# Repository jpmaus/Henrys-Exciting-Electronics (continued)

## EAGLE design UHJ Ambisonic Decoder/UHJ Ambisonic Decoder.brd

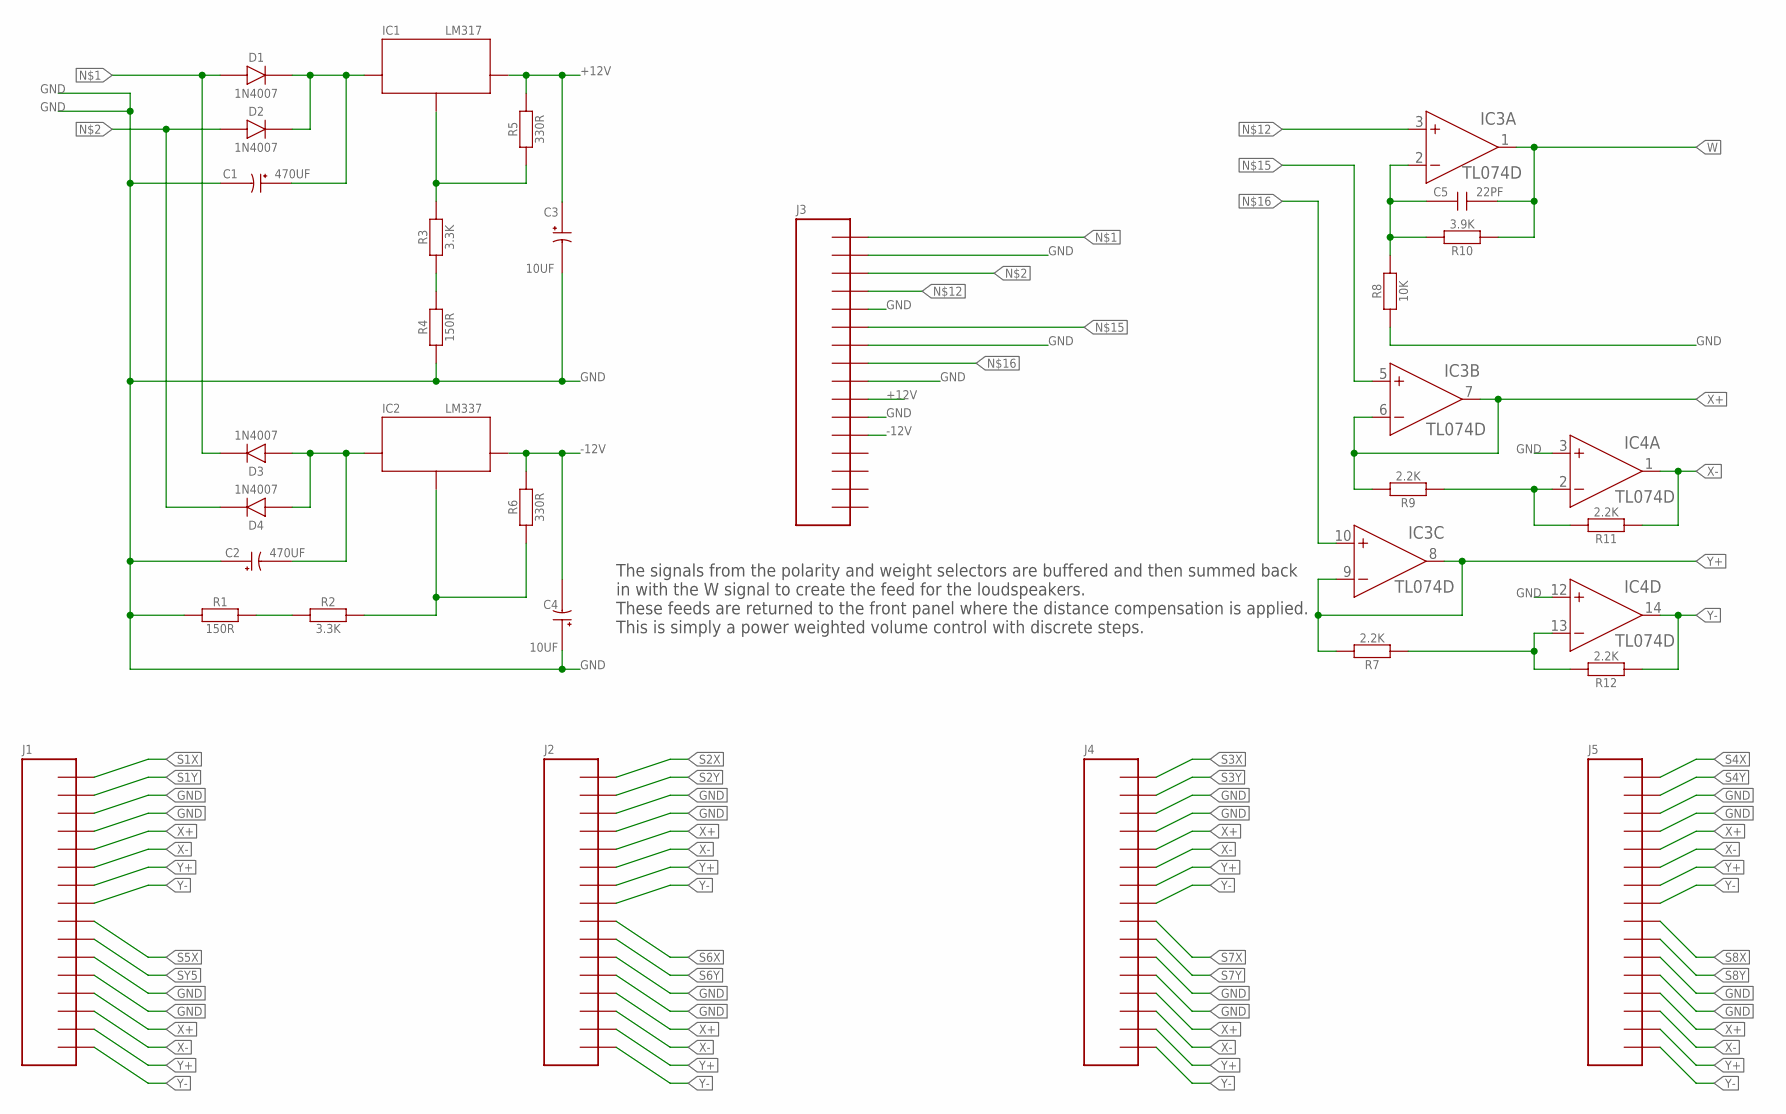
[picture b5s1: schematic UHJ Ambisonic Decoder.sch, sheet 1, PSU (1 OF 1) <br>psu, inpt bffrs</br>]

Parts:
C1, C2: 470UF; PANASONIC_E
C3, C4: 10UF; PANASONIC_E
C5: 22PF; CT6032
D1, D2, D3, D4: 1N4007; SOD123
IC1: LM317; SO08
IC2: LM337; SO08
IC3, IC4: TL074D; SO14
J1, J2, J3, J4, J5: CON_16; 2X08SMT
R1, R4: 150R; R6332W
R2, R3: 3.3K; R6332W
R5, R6: 330R; R6332W
R7, R9, R11, R12: 2.2K; R6332W
R8: 10K; R6332W
R10: 3.9K; R6332W

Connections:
+12V: C3.+ (1), IC1.1 (OUT), IC3.4 (V+), IC4.4 (V+), J3.10, R5.2; also elsewhere on the board
-12V: C4.- (2), IC2.1 (OUT), IC3.11 (V-), IC4.11 (V-), J3.12, R6.2; also elsewhere on the board
GND: C1.- (2), C2.+ (1), C3.- (2), C4.+ (1), IC4.3 (+IN), IC4.12 (+IN), J1.3, J1.4, J1.11, J1.12, J2.3, J2.4, J2.11, J2.12, J3.2, J3.5, J3.7, J3.9, J3.11, J4.3, J4.4, J4.11, J4.12, J5.3, J5.4, J5.11, J5.12, R1.1, R4.1, R8.1; also elsewhere on the board
unnamed: D1.A, D3.C, J3.1
unnamed: D2.A, D4.C, J3.3
unnamed: C1.+ (1), D1.C, D2.C, IC1.8 (IN)
unnamed: C2.- (2), D3.A, D4.A, IC2.8 (IN)
unnamed: IC1.2 (GND), IC1.3 (GND), IC1.6 (GND), IC1.7 (GND), R3.2, R5.1
unnamed: R3.1, R4.2
unnamed: IC2.2 (GND), IC2.3 (GND), IC2.6 (GND), IC2.7 (GND), R2.2, R6.1
unnamed: IC3.3 (+IN), J3.4
unnamed: C5.- (2), IC3.2 (-IN), R8.2, R10.2
unnamed: IC3.5 (+IN), J3.6
unnamed: IC3.10 (+IN), J3.8
unnamed: IC4.2 (-IN), R9.1, R11.2
unnamed: IC4.13 (-IN), R7.1, R12.2
unnamed: R1.2, R2.1
S1X: J1.1; also elsewhere on the board
S1Y: J1.2; also elsewhere on the board
S2X: J2.1; also elsewhere on the board
S2Y: J2.2; also elsewhere on the board
S3X: J4.1; also elsewhere on the board
S3Y: J4.2; also elsewhere on the board
S4X: J5.1; also elsewhere on the board
S4Y: J5.2; also elsewhere on the board
S5X: J1.9; also elsewhere on the board
S6X: J2.9; also elsewhere on the board
S6Y: J2.10; also elsewhere on the board
S7X: J4.9; also elsewhere on the board
S7Y: J4.10; also elsewhere on the board
S8X: J5.9; also elsewhere on the board
S8Y: J5.10; also elsewhere on the board
SY5: J1.10; also elsewhere on the board
W: C5.+ (1), IC3.1 (OUT), R10.1; also elsewhere on the board
X+: IC3.6 (-IN), IC3.7 (OUT), J1.5, J1.13, J2.5, J2.13, J4.5, J4.13, J5.5, J5.13, R9.2; also elsewhere on the board
X-: IC4.1 (OUT), J1.6, J1.14, J2.6, J2.14, J4.6, J4.14, J5.6, J5.14, R11.1; also elsewhere on the board
Y+: IC3.8 (OUT), IC3.9 (-IN), J1.7, J1.15, J2.7, J2.15, J4.7, J4.15, J5.7, J5.15, R7.2; also elsewhere on the board
Y-: IC4.14 (OUT), J1.8, J1.16, J2.8, J2.16, J4.8, J4.16, J5.8, J5.16, R12.1; also elsewhere on the board

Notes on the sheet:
The signals from the polarity and weight selectors are buffered and then summed back in with the W signal to create the feed for the loudspeakers. These feeds are returned to the front panel where the distance compensation is applied. This is simply a power weighted volume control with discrete ste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

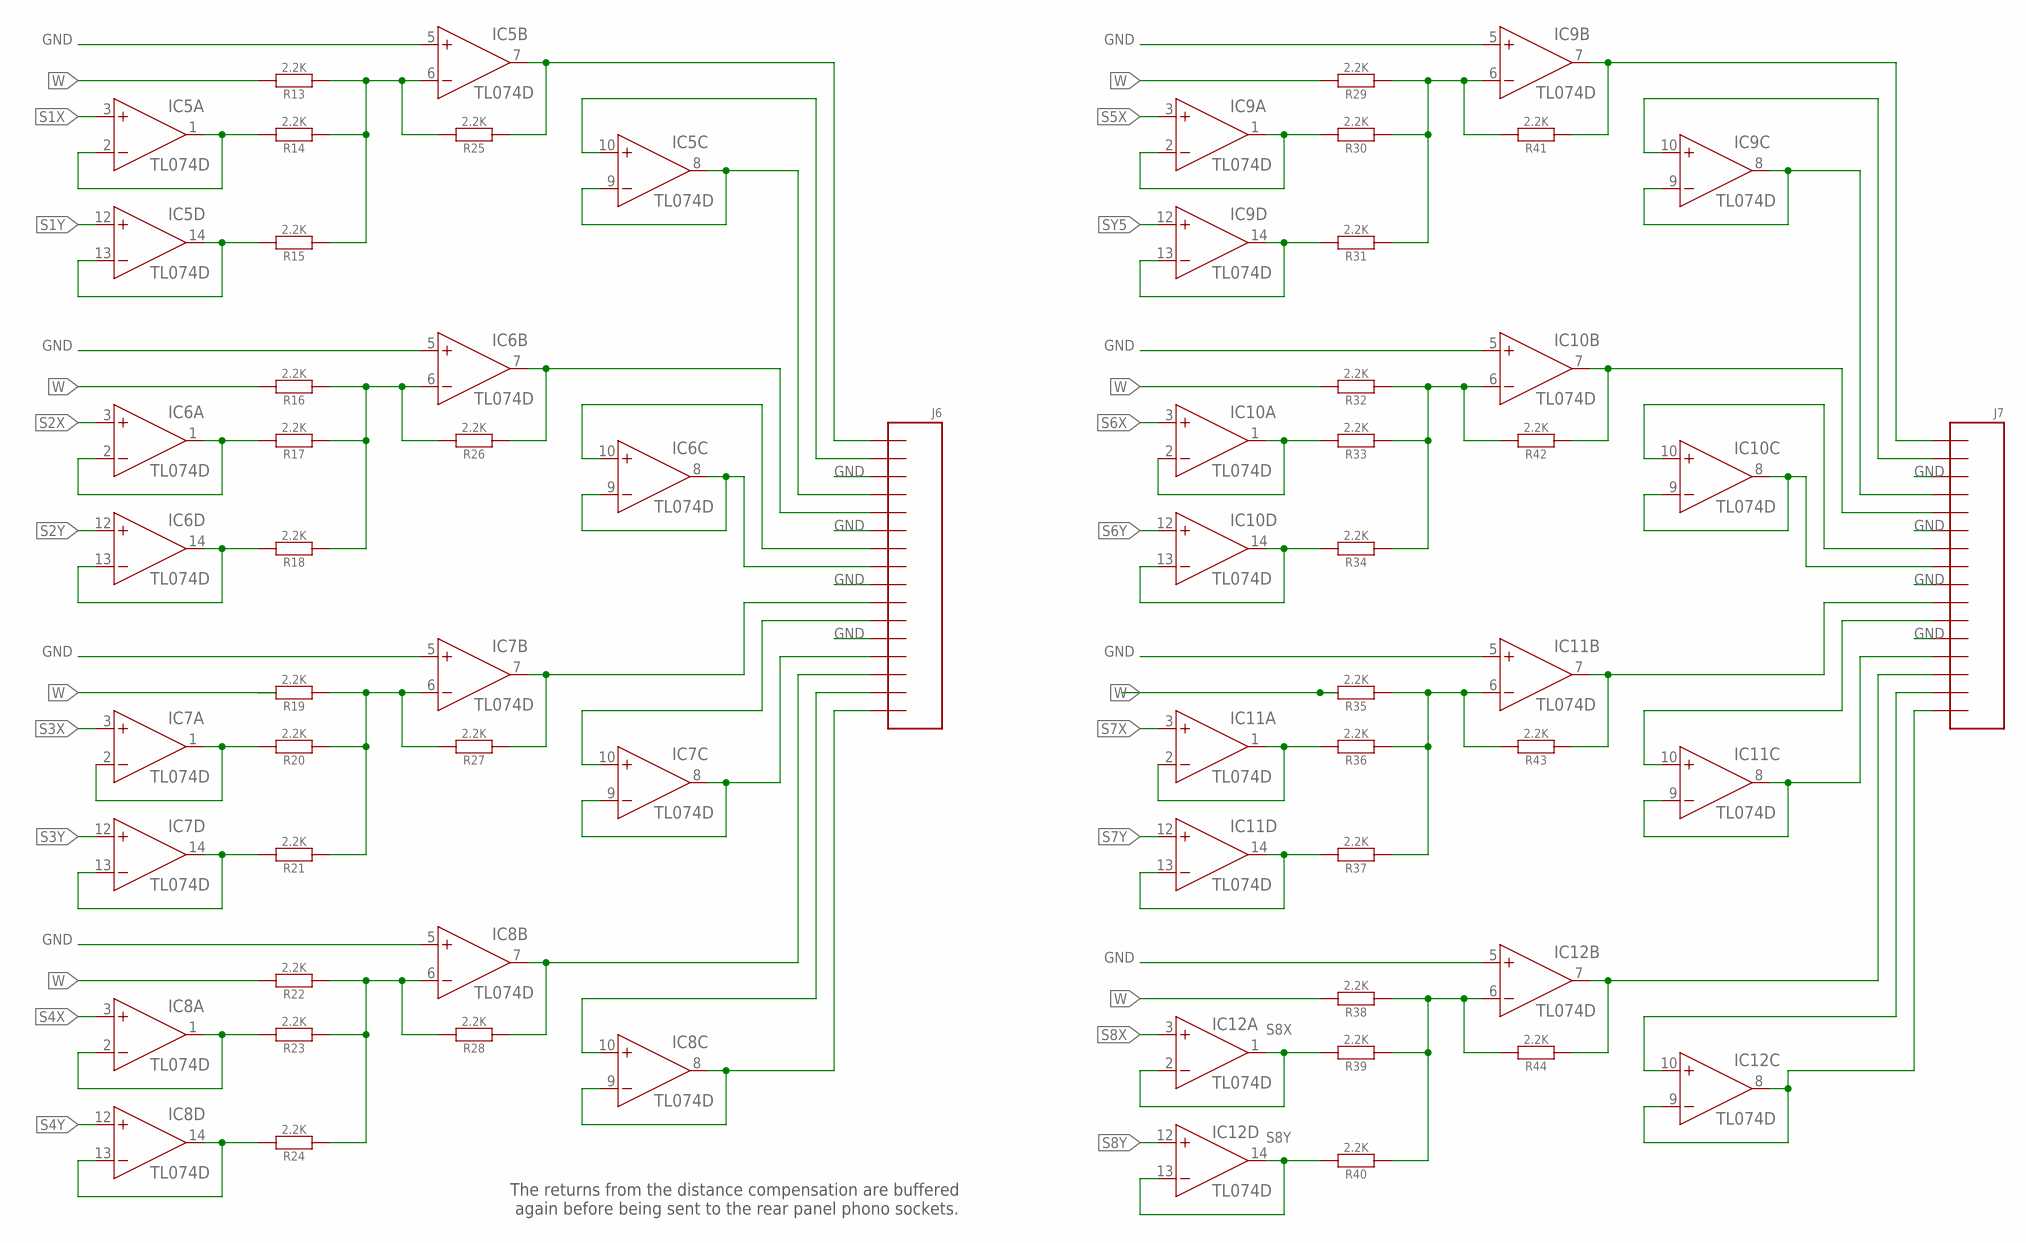
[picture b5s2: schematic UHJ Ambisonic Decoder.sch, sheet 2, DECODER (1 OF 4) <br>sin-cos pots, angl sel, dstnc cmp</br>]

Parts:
IC5, IC6, IC7, IC8, IC9, IC10, IC11, IC12: TL074D; SO14
J6, J7: CON_16; 2X08SMT
R13, R14, R15, R16, R17, R18, R19, R20, R21, R22, R23, R24, R25, R26, R27, R28, R29, R30, R31, R32, R33, R34, R35, R36, R37, R38, R39, R40, R41, R42, R43, R44: 2.2K; R6332W

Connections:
GND: IC5.5 (+IN), IC6.5 (+IN), IC7.5 (+IN), IC8.5 (+IN), IC9.5 (+IN), IC10.5 (+IN), IC11.5 (+IN), IC12.5 (+IN), J6.3, J6.6, J6.9, J6.12, J7.3, J7.6, J7.9, J7.12; also elsewhere on the board
unnamed: IC5.8 (OUT), IC5.9 (-IN), J6.4
unnamed: IC7.8 (OUT), IC7.9 (-IN), J6.13
unnamed: IC6.8 (OUT), IC6.9 (-IN), J6.8
unnamed: IC9.1 (OUT), IC9.2 (-IN), R30.2
unnamed: IC6.1 (OUT), IC6.2 (-IN), R17.2
unnamed: IC6.13 (-IN), IC6.14 (OUT), R18.2
unnamed: IC5.10 (+IN), J6.2
unnamed: IC6.10 (+IN), J6.7
unnamed: IC9.7 (OUT), J7.1, R41.1
unnamed: IC6.6 (-IN), R16.1, R17.1, R18.1, R26.2
unnamed: IC9.13 (-IN), IC9.14 (OUT), R31.2
unnamed: IC5.13 (-IN), IC5.14 (OUT), R15.2
unnamed: IC5.6 (-IN), R13.1, R14.1, R15.1, R25.2
unnamed: IC5.7 (OUT), J6.1, R25.1
unnamed: IC5.1 (OUT), IC5.2 (-IN), R14.2
unnamed: IC6.7 (OUT), J6.5, R26.1
unnamed: IC8.1 (OUT), IC8.2 (-IN), R23.2
unnamed: IC8.13 (-IN), IC8.14 (OUT), R24.2
unnamed: IC8.6 (-IN), R22.1, R23.1, R24.1, R28.2
unnamed: IC8.10 (+IN), J6.15
unnamed: IC7.13 (-IN), IC7.14 (OUT), R21.2
unnamed: IC7.6 (-IN), R19.1, R20.1, R21.1, R27.2
unnamed: IC7.7 (OUT), J6.10, R27.1
unnamed: IC7.1 (OUT), IC7.2 (-IN), R20.2
unnamed: IC8.7 (OUT), J6.14, R28.1
unnamed: IC10.10 (+IN), J7.7
unnamed: IC9.6 (-IN), R29.1, R30.1, R31.1, R41.2
unnamed: IC10.13 (-IN), IC10.14 (OUT), R34.2
unnamed: IC12.10 (+IN), J7.15
unnamed: IC10.6 (-IN), R32.1, R33.1, R34.1, R42.2
unnamed: IC12.8 (OUT), IC12.9 (-IN), J7.16
unnamed: IC10.7 (OUT), J7.5, R42.1
unnamed: IC10.1 (OUT), IC10.2 (-IN), R33.2
unnamed: IC12.1 (OUT), IC12.2 (-IN), R39.2
unnamed: IC12.13 (-IN), IC12.14 (OUT), R40.2
unnamed: IC12.6 (-IN), R38.1, R39.1, R40.1, R44.2
unnamed: IC11.8 (OUT), IC11.9 (-IN), J7.13
unnamed: IC11.13 (-IN), IC11.14 (OUT), R37.2
unnamed: IC11.6 (-IN), R35.1, R36.1, R37.1, R43.2
unnamed: IC11.7 (OUT), J7.10, R43.1
unnamed: IC11.1 (OUT), IC11.2 (-IN), R36.2
unnamed: IC8.8 (OUT), IC8.9 (-IN), J6.16
unnamed: IC9.8 (OUT), IC9.9 (-IN), J7.4
unnamed: IC7.10 (+IN), J6.11
unnamed: IC12.7 (OUT), J7.14, R44.1
unnamed: IC10.8 (OUT), IC10.9 (-IN), J7.8
unnamed: IC9.10 (+IN), J7.2
unnamed: IC11.10 (+IN), J7.11
S1X: IC5.3 (+IN); also elsewhere on the board
S1Y: IC5.12 (+IN); also elsewhere on the board
S2X: IC6.3 (+IN); also elsewhere on the board
S2Y: IC6.12 (+IN); also elsewhere on the board
S3X: IC7.3 (+IN); also elsewhere on the board
S3Y: IC7.12 (+IN); also elsewhere on the board
S4X: IC8.3 (+IN); also elsewhere on the board
S4Y: IC8.12 (+IN); also elsewhere on the board
S5X: IC9.3 (+IN); also elsewhere on the board
S6X: IC10.3 (+IN); also elsewhere on the board
S6Y: IC10.12 (+IN); also elsewhere on the board
S7X: IC11.3 (+IN); also elsewhere on the board
S7Y: IC11.12 (+IN); also elsewhere on the board
S8X: IC12.3 (+IN); also elsewhere on the board
S8Y: IC12.12 (+IN); also elsewhere on the board
SY5: IC9.12 (+IN); also elsewhere on the board
W: R13.2, R16.2, R19.2, R22.2, R29.2, R32.2, R35.2, R38.2; also elsewhere on the board

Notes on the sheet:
The returns from the distance compensation are buffered again before being sent to the rear panel phono sockets.

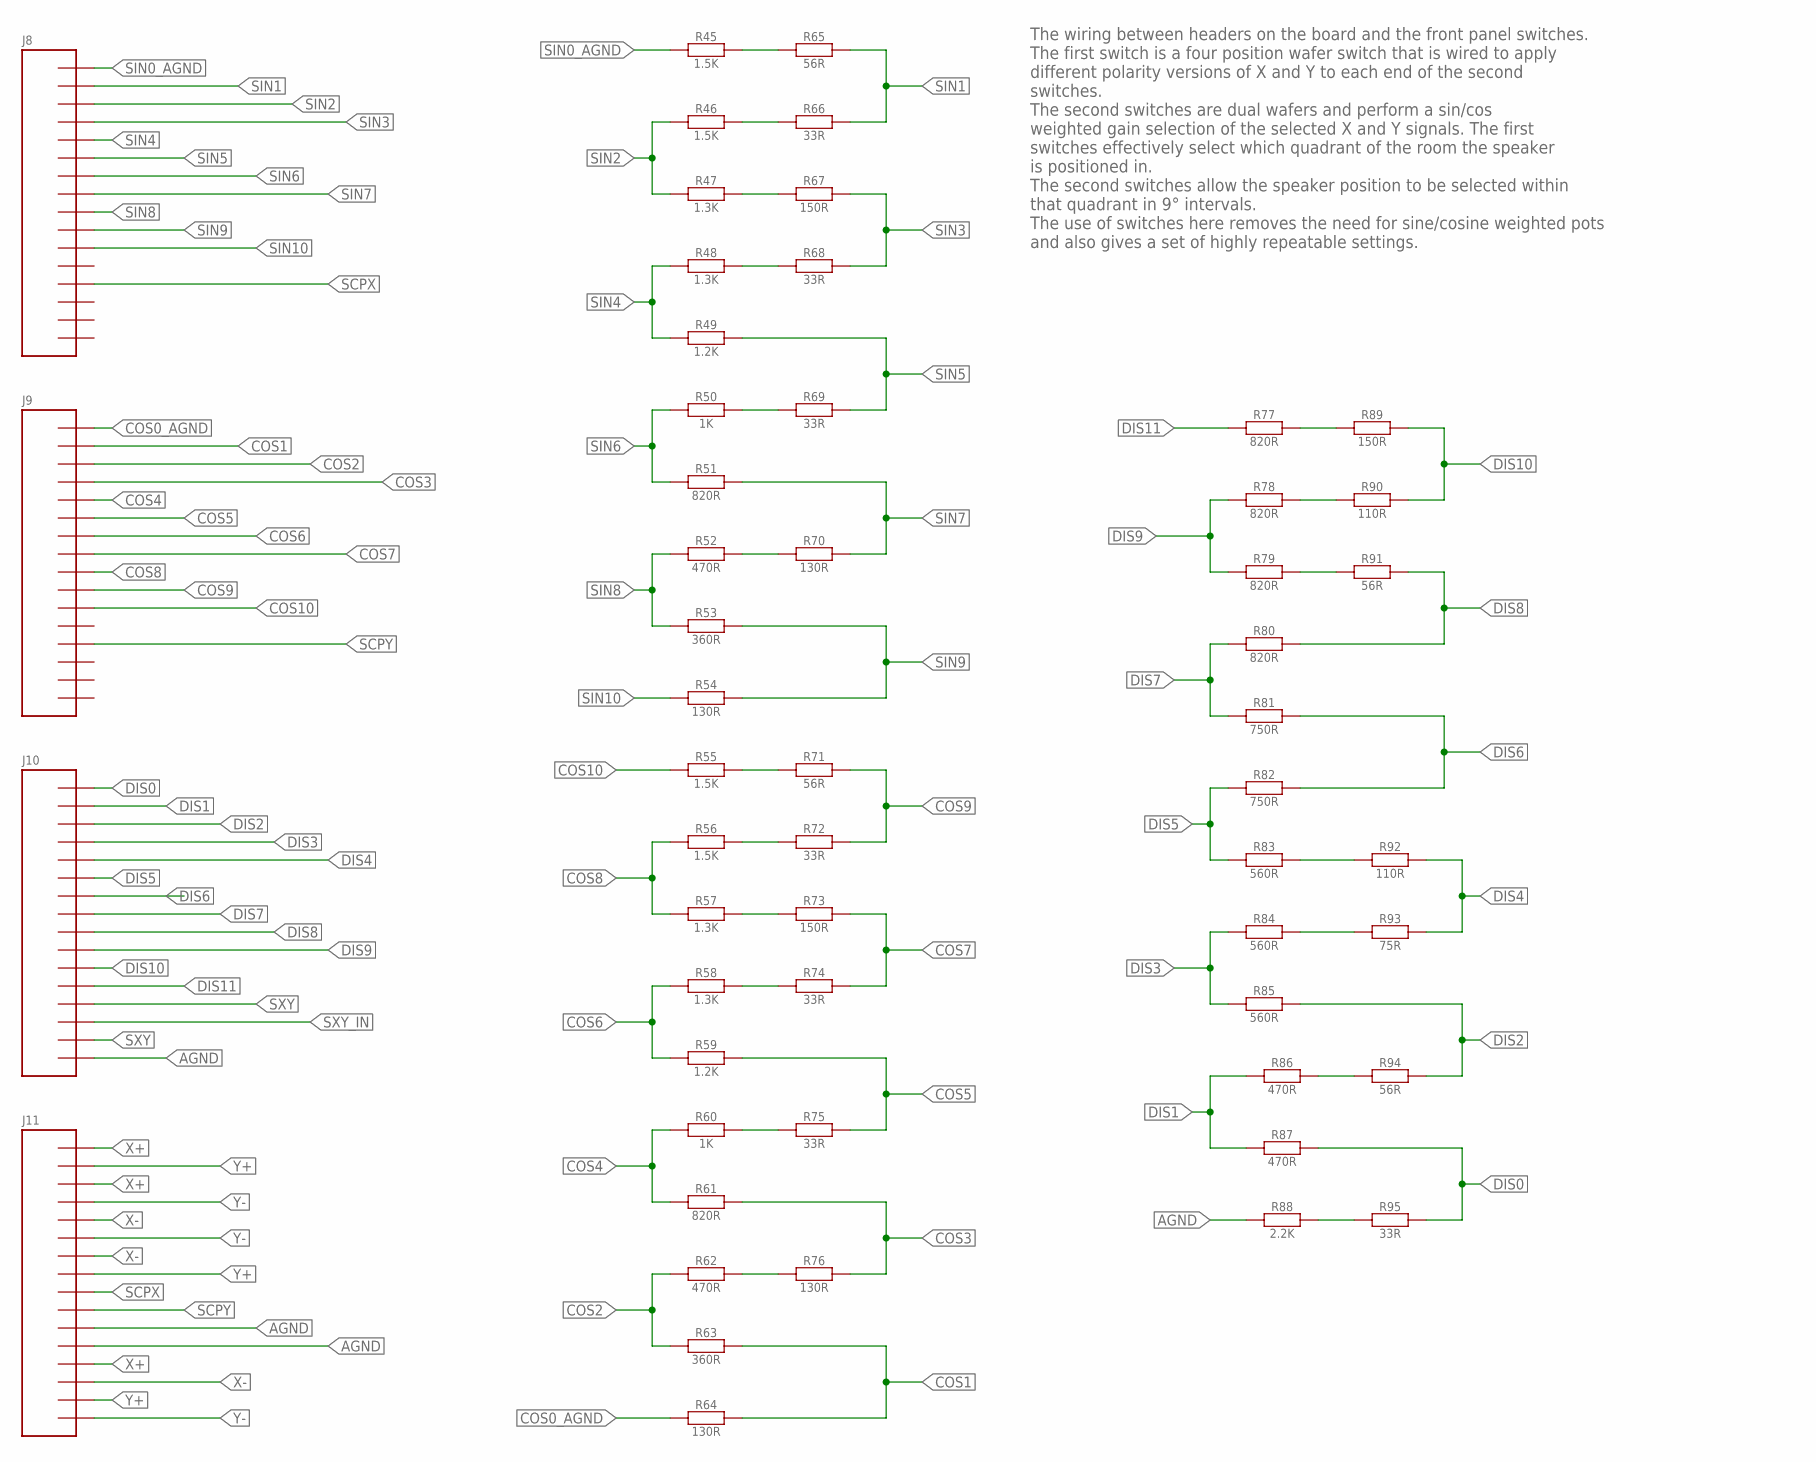
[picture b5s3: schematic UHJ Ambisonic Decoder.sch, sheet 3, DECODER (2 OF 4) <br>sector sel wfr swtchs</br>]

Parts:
J8, J9, J10, J11: CON_16; 2X08SMT
R45, R46, R55, R56: 1.5K; R6332W
R47, R48, R57, R58: 1.3K; R6332W
R49, R59: 1.2K; R6332W
R50, R60: 1K; R6332W
R51, R61, R77, R78, R79, R80: 820R; R6332W
R52, R62, R86, R87: 470R; R6332W
R53, R63: 360R; R6332W
R54, R64, R70, R76: 130R; R6332W
R65, R71, R91, R94: 56R; R6332W
R66, R68, R69, R72, R74, R75, R95: 33R; R6332W
R67, R73, R89: 150R; R6332W
R81, R82: 750R; R6332W
R83, R84, R85: 560R; R6332W
R88: 2.2K; R6332W
R90, R92: 110R; R6332W
R93: 75R; R6332W

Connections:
AGND: J10.16, J11.11, J11.12, R88.1
COS0_AGND: J9.1, R64.1
COS1: J9.2, R63.2, R64.2
COS2: J9.3, R62.1, R63.1
COS3: J9.4, R61.2, R76.2
COS4: J9.5, R60.1, R61.1
COS5: J9.6, R59.2, R75.2
COS6: J9.7, R58.1, R59.1
COS7: J9.8, R73.2, R74.2
COS8: J9.9, R56.1, R57.1
COS9: J9.10, R71.2, R72.2
COS10: J9.11, R55.1
DIS0: J10.1, R87.2, R95.2
DIS1: J10.2, R86.1, R87.1
DIS2: J10.3, R85.2, R94.2
DIS3: J10.4, R84.1, R85.1
DIS4: J10.5, R92.2, R93.2
DIS5: J10.6, R82.1, R83.1
DIS6: J10.7, R81.2, R82.2
DIS7: J10.8, R80.1, R81.1
DIS8: J10.9, R80.2, R91.2
DIS9: J10.10, R78.1, R79.1
DIS10: J10.11, R89.2, R90.2
DIS11: J10.12, R77.1
unnamed: R45.2, R65.1
unnamed: R46.2, R66.1
unnamed: R47.2, R67.1
unnamed: R48.2, R68.1
unnamed: R50.2, R69.1
unnamed: R52.2, R70.1
unnamed: R55.2, R71.1
unnamed: R56.2, R72.1
unnamed: R57.2, R73.1
unnamed: R58.2, R74.1
unnamed: R60.2, R75.1
unnamed: R62.2, R76.1
unnamed: R77.2, R89.1
unnamed: R78.2, R90.1
unnamed: R79.2, R91.1
unnamed: R83.2, R92.1
unnamed: R84.2, R93.1
unnamed: R86.2, R94.1
unnamed: R88.2, R95.1
SCPX: J8.13, J11.9
SCPY: J9.13, J11.10
SIN0_AGND: J8.1, R45.1
SIN1: J8.2, R65.2, R66.2
SIN2: J8.3, R46.1, R47.1
SIN3: J8.4, R67.2, R68.2
SIN4: J8.5, R48.1, R49.1
SIN5: J8.6, R49.2, R69.2
SIN6: J8.7, R50.1, R51.1
SIN7: J8.8, R51.2, R70.2
SIN8: J8.9, R52.1, R53.1
SIN9: J8.10, R53.2, R54.2
SIN10: J8.11, R54.1
SXY: J10.13, J10.15
SXY_IN: J10.14
X+: J11.1, J11.3, J11.13; also elsewhere on the board
X-: J11.5, J11.7, J11.14; also elsewhere on the board
Y+: J11.2, J11.8, J11.15; also elsewhere on the board
Y-: J11.4, J11.6, J11.16; also elsewhere on the board

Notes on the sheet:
The wiring between headers on the board and the front panel switches. The first switch is a four position wafer switch that is wired to apply different polarity versions of X and Y to each end of the second switches. The second switches are dual wafers and perform a sin/cos weighted gain selection 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

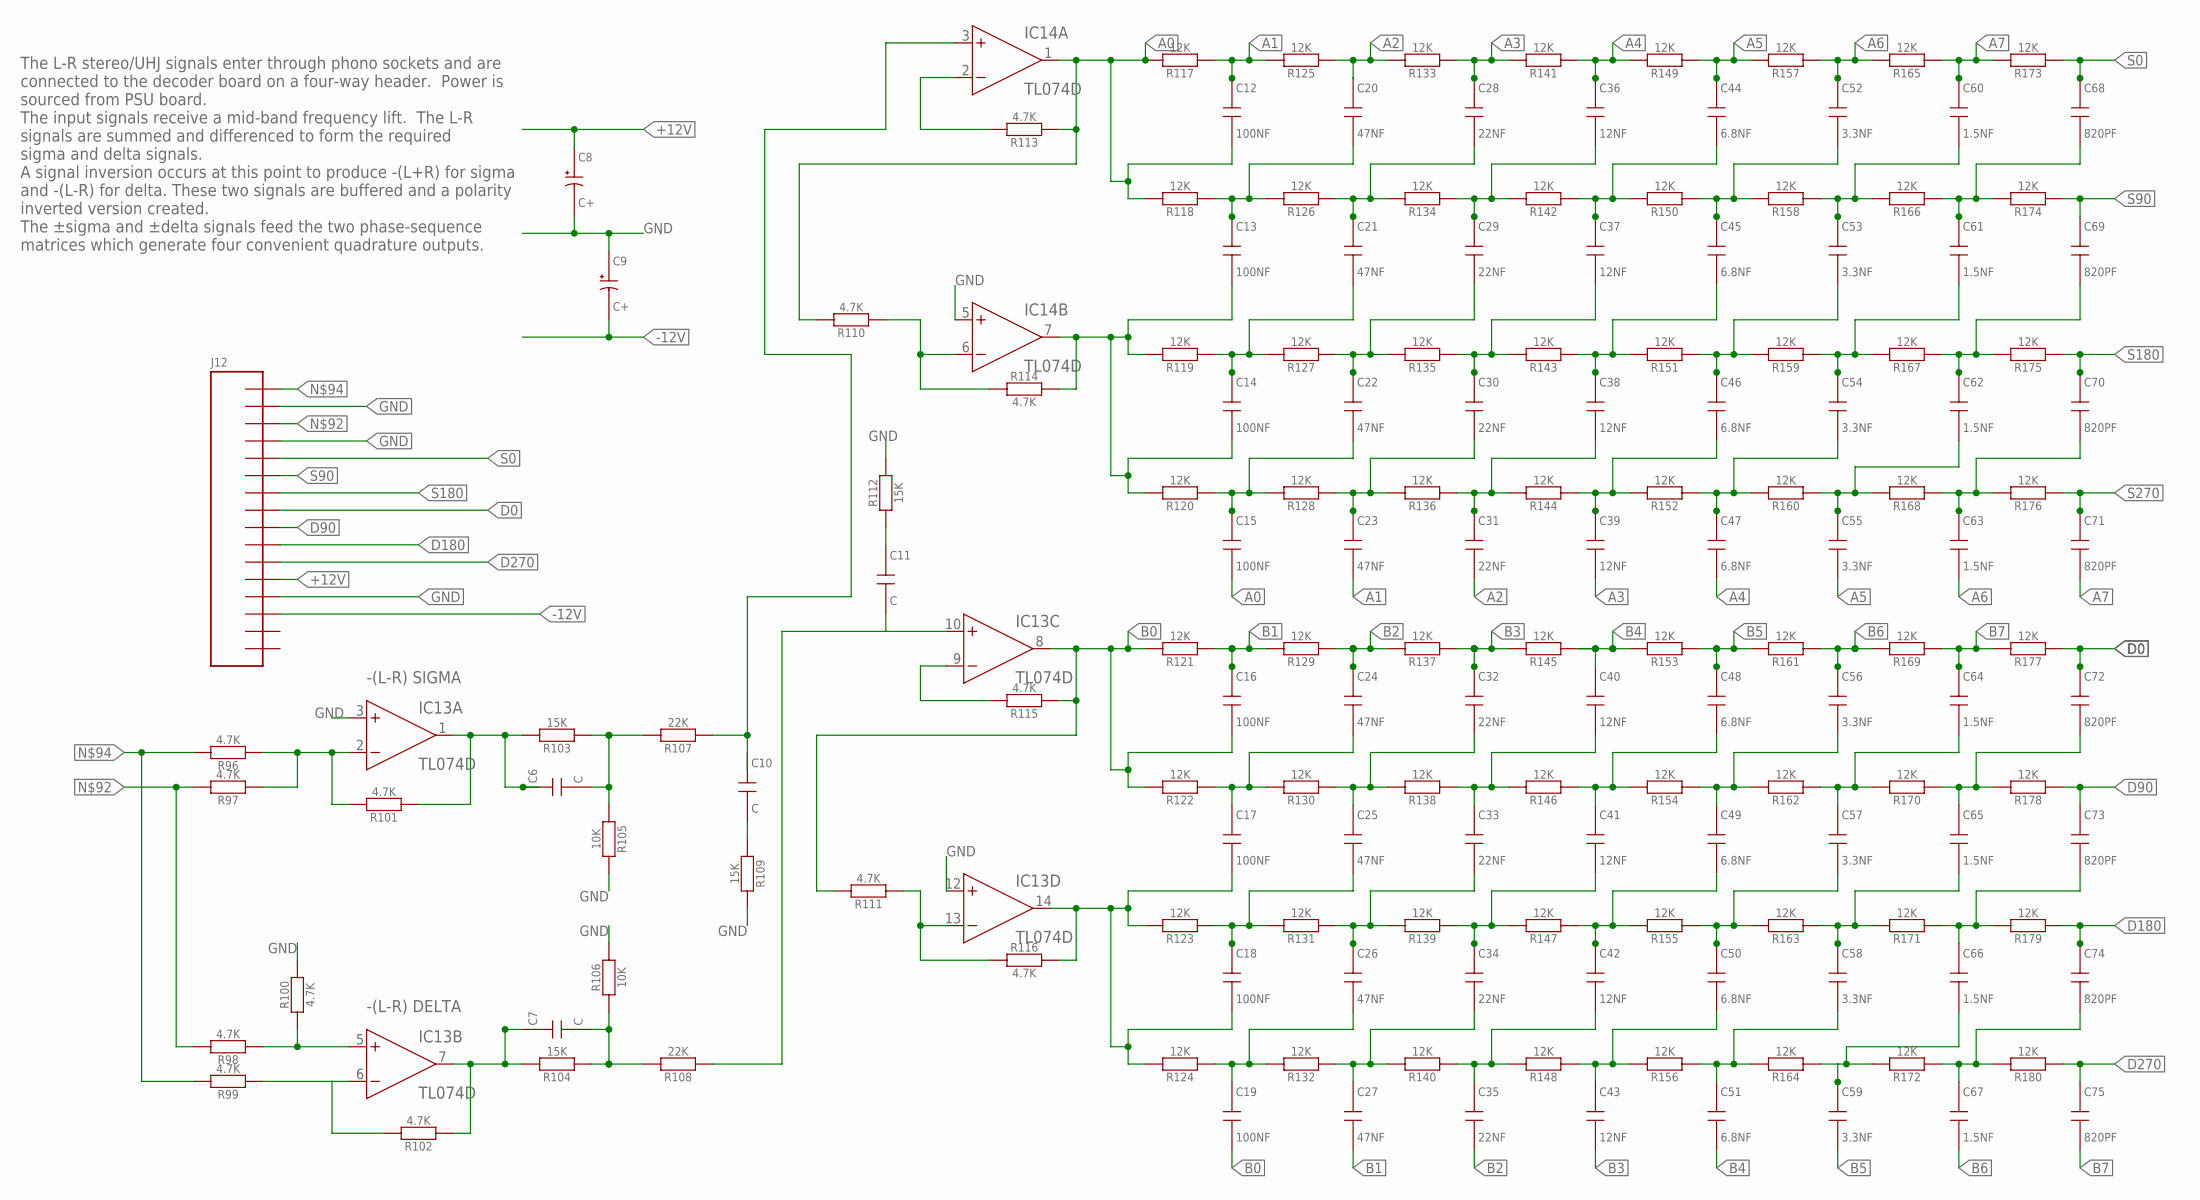
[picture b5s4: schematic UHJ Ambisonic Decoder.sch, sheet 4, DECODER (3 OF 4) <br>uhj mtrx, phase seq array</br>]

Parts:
C6, C7, C10, C11: C; CT6032
C8, C9: C+; PANASONIC_E
C12, C13, C14, C15, C16, C17, C18, C19: 100NF; CT6032
C20, C21, C22, C23, C24, C25, C26, C27: 47NF; CT6032
C28, C29, C30, C31, C32, C33, C34, C35: 22NF; CT6032
C36, C37, C38, C39, C40, C41, C42, C43: 12NF; CT6032
C44, C45, C46, C47, C48, C49, C50, C51: 6.8NF; CT6032
C52, C53, C54, C55, C56, C57, C58, C59: 3.3NF; CT6032
C60, C61, C62, C63, C64, C65, C66, C67: 1.5NF; CT6032
C68, C69, C70, C71, C72, C73, C74, C75: 820PF; CT6032
IC13, IC14: TL074D; SO14
J12: CON_16; 2X08SMT
R96, R97, R98, R99, R100, R101, R102, R110, R111, R113, R114, R115, R116: 4.7K; R6332W
R103, R104, R109, R112: 15K; R6332W
R105, R106: 10K; R6332W
R107, R108: 22K; R6332W
R117, R118, R119, R120, R121, R122, R123, R124, R125, R126, R127, R128, R129, R130, R131, R132, R133, R134, R135, R136, R137, R138, R139, R140, R141, R142, R143, R144, R145, R146, R147, R148, R149, R150, R151, R152, R153, R154, R155, R156, R157, R158, R159, R160, R161, R162, R163, R164, R165, R166, R167, R168, R169, R170, R171, R172, R173, R174, R175, R176, R177, R178, R179, R180: 12K; R6332W

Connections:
+12V: C8.+ (1), IC13.4 (V+), IC14.4 (V+), J12.12; also elsewhere on the board
-12V: C9.- (2), IC13.11 (V-), IC14.11 (V-), J12.14; also elsewhere on the board
A0: C12.- (2), C15.- (2), IC14.1 (OUT), R110.2, R113.1, R117.2, R118.2
A1: C12.+ (1), C23.- (2), R117.1, R125.2
A2: C20.+ (1), C31.- (2), R125.1, R133.2
A3: C28.+ (1), C39.- (2), R133.1, R141.2
A4: C36.+ (1), C47.- (2), R141.1, R149.2
A5: C44.+ (1), C55.- (2), R149.1, R157.2
A6: C52.+ (1), C63.- (2), R157.1, R165.2
A7: C60.+ (1), C71.- (2), R165.1, R173.2
B0: C16.- (2), C19.- (2), IC13.8 (OUT), R111.2, R115.1, R121.2, R122.2
B1: C16.+ (1), C27.- (2), R121.1, R129.2
B2: C24.+ (1), C35.- (2), R129.1, R137.2
B3: C32.+ (1), C43.- (2), R137.1, R145.2
B4: C40.+ (1), C51.- (2), R145.1, R153.2
B5: C48.+ (1), C59.- (2), R153.1, R161.2
B6: C56.+ (1), C67.- (2), R161.1, R169.2
B7: C64.+ (1), C75.- (2), R169.1, R177.2
D0: C72.+ (1), J12.8, R177.1; also elsewhere on the board
D90: C73.+ (1), J12.9, R178.1; also elsewhere on the board
D180: C74.+ (1), J12.10, R179.1
D270: C75.+ (1), J12.11, R180.1
GND: C8.- (2), C9.+ (1), IC13.3 (+IN), IC14.5 (+IN), J12.2, J12.4, J12.13, R100.2, R105.2, R106.2, R109.2, R112.2; also elsewhere on the board
unnamed: C59.+ (1), C66.- (2), R164.1, R172.2
unnamed: C65.+ (1), C72.- (2), R170.1, R178.2
unnamed: C55.+ (1), C62.- (2), R160.1, R168.2
unnamed: C13.+ (1), C20.- (2), R118.1, R126.2
unnamed: C21.+ (1), C28.- (2), R126.1, R134.2
unnamed: C29.+ (1), C36.- (2), R134.1, R142.2
unnamed: C37.+ (1), C44.- (2), R142.1, R150.2
unnamed: C45.+ (1), C52.- (2), R150.1, R158.2
unnamed: C53.+ (1), C60.- (2), R158.1, R166.2
unnamed: C61.+ (1), C68.- (2), R166.1, R174.2
unnamed: C14.+ (1), C21.- (2), R119.1, R127.2
unnamed: C22.+ (1), C29.- (2), R127.1, R135.2
unnamed: C30.+ (1), C37.- (2), R135.1, R143.2
unnamed: C38.+ (1), C45.- (2), R143.1, R151.2
unnamed: C46.+ (1), C53.- (2), R151.1, R159.2
unnamed: C54.+ (1), C61.- (2), R159.1, R167.2
unnamed: C62.+ (1), C69.- (2), R167.1, R175.2
unnamed: C15.+ (1), C22.- (2), R120.1, R128.2
unnamed: C23.+ (1), C30.- (2), R128.1, R136.2
unnamed: C31.+ (1), C38.- (2), R136.1, R144.2
unnamed: C39.+ (1), C46.- (2), R144.1, R152.2
unnamed: C47.+ (1), C54.- (2), R152.1, R160.2
unnamed: C63.+ (1), C70.- (2), R168.1, R176.2
unnamed: C17.+ (1), C24.- (2), R122.1, R130.2
unnamed: C25.+ (1), C32.- (2), R130.1, R138.2
unnamed: C33.+ (1), C40.- (2), R138.1, R146.2
unnamed: C41.+ (1), C48.- (2), R146.1, R154.2
unnamed: C49.+ (1), C56.- (2), R154.1, R162.2
unnamed: C57.+ (1), C64.- (2), R162.1, R170.2
unnamed: C18.+ (1), C25.- (2), R123.1, R131.2
unnamed: C26.+ (1), C33.- (2), R131.1, R139.2
unnamed: C34.+ (1), C41.- (2), R139.1, R147.2
unnamed: C42.+ (1), C49.- (2), R147.1, R155.2
unnamed: C50.+ (1), C57.- (2), R155.1, R163.2
unnamed: C58.+ (1), C65.- (2), R163.1, R171.2
unnamed: C66.+ (1), C73.- (2), R171.1, R179.2
unnamed: C19.+ (1), C26.- (2), R124.1, R132.2
unnamed: C27.+ (1), C34.- (2), R132.1, R140.2
unnamed: C35.+ (1), C42.- (2), R140.1, R148.2
unnamed: C43.+ (1), C50.- (2), R148.1, R156.2
unnamed: C51.+ (1), C58.- (2), R156.1, R164.2
unnamed: IC13.2 (-IN), R96.1, R97.1, R101.2
unnamed: IC13.6 (-IN), R99.1, R102.2
unnamed: J12.3, R97.2, R98.2
unnamed: IC13.5 (+IN), R98.1, R100.1
unnamed: J12.1, R96.2, R99.2
unnamed: C67.+ (1), C74.- (2), R172.1, R180.2
unnamed: IC13.9 (-IN), R115.2
unnamed: C17.- (2), C18.- (2), IC13.14 (OUT), R116.2, R123.2, R124.2
unnamed: IC13.13 (-IN), R111.1, R116.1
unnamed: C6.- (2), R103.1, R105.1, R107.2
unnamed: C10.+ (1), IC14.3 (+IN), R107.1
unnamed: C10.- (2), R109.1
unnamed: C7.- (2), R104.1, R106.1, R108.2
unnamed: C11.- (2), IC13.10 (+IN), R108.1
unnamed: C11.+ (1), R112.1
unnamed: IC14.2 (-IN), R113.2
unnamed: C13.- (2), C14.- (2), IC14.7 (OUT), R114.2, R119.2, R120.2
unnamed: IC14.6 (-IN), R110.1, R114.1
S0: C68.+ (1), J12.5, R173.1; also elsewhere on the board
S90: C69.+ (1), J12.6, R174.1; also elsewhere on the board
S180: C70.+ (1), J12.7, R175.1
S270: C71.+ (1), R176.1
X-: C6.+ (1), IC13.1 (OUT), R101.1, R103.2; also elsewhere on the board
Y-: C7.+ (1), IC13.7 (OUT), R102.1, R104.2; also elsewhere on the board

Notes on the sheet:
The L-R stereo/UHJ signals enter through phono sockets and are connected to the decoder board on a four-way header. Power is sourced from PSU board. The input signals receive a mid-band frequency lift. The L-R signals are summed and differenced to form the required sigma and delta signals. A signal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
-(L-R) SIGMA
-(L-R) DELTA

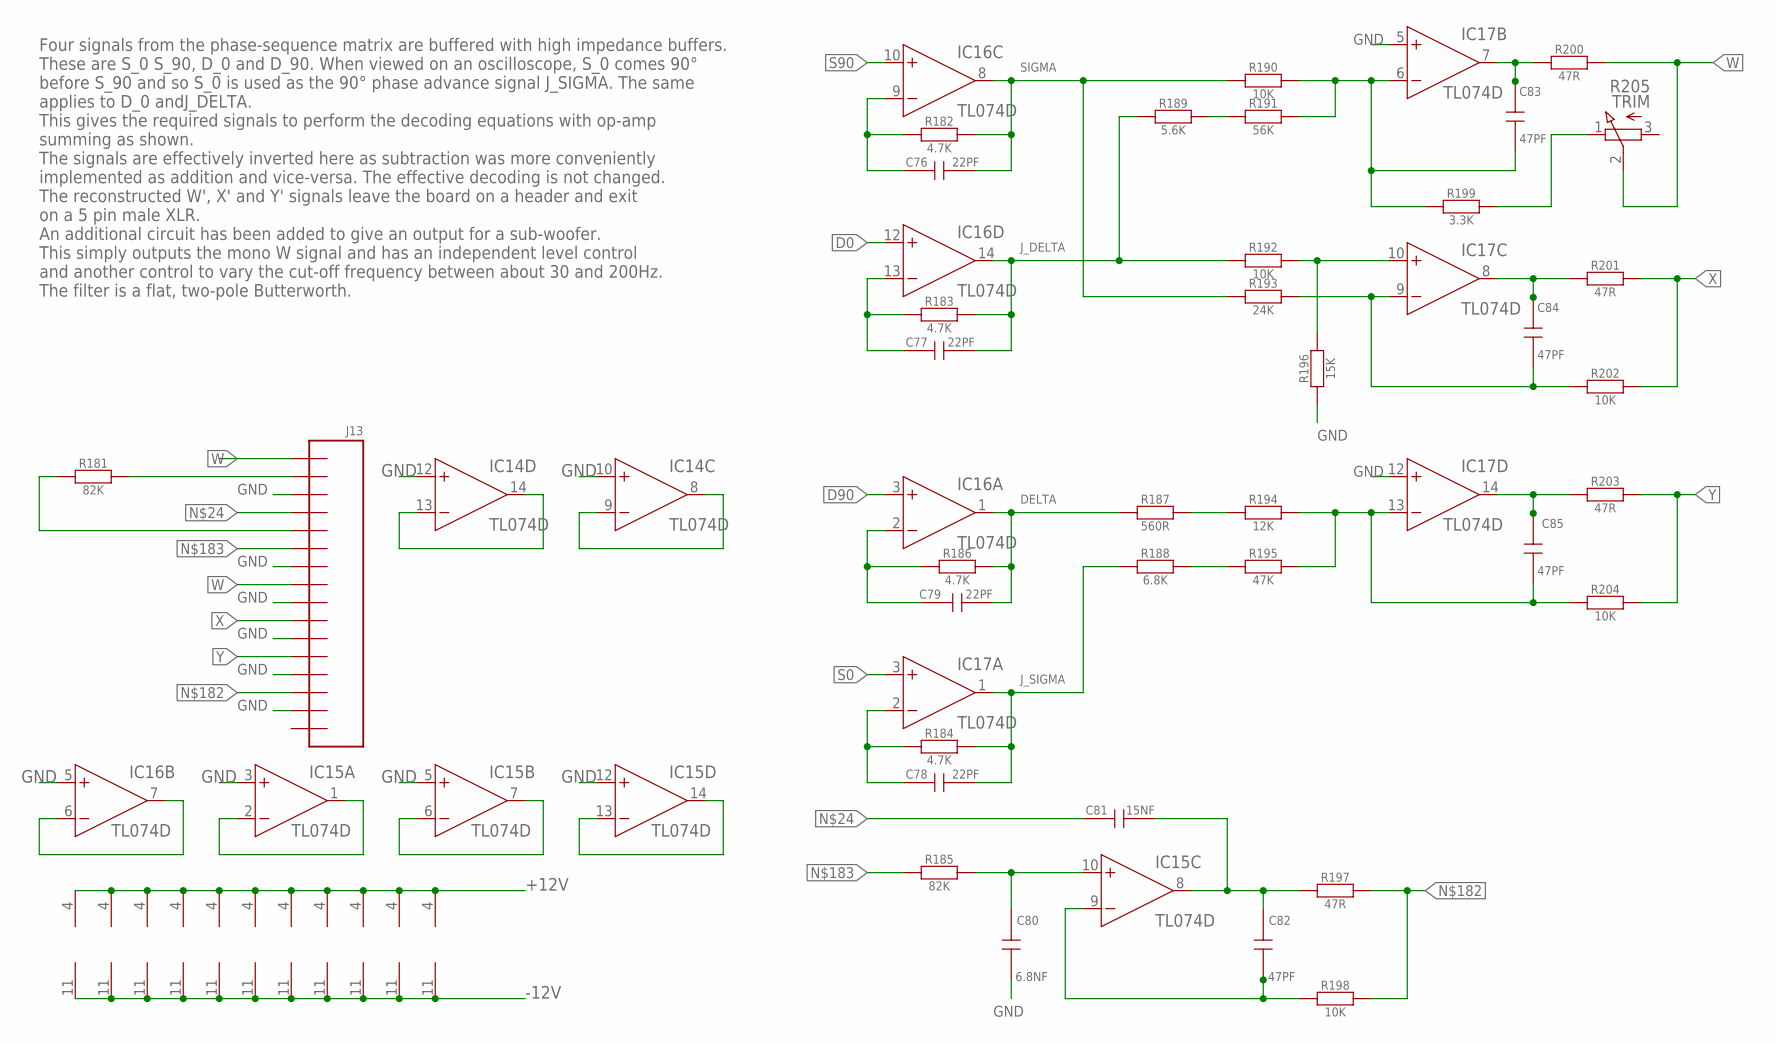
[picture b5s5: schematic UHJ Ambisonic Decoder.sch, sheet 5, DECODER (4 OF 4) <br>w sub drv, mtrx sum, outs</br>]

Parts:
C76, C77, C78, C79: 22PF; CT6032
C80: 6.8NF; CT6032
C81: 15NF; CT6032
C82, C83, C84, C85: 47PF; CT6032
IC5, IC6, IC7, IC8, IC9, IC10, IC11, IC12, IC14, IC15, IC16, IC17: TL074D; SO14
J13: CON_16; 2X08SMT
R181, R185: 82K; R6332W
R182, R183, R184, R186: 4.7K; R6332W
R187: 560R; R6332W
R188: 6.8K; R6332W
R189: 5.6K; R6332W
R190, R192, R198, R202, R204: 10K; R6332W
R191: 56K; R6332W
R193: 24K; R6332W
R194: 12K; R6332W
R195: 47K; R6332W
R196: 15K; R6332W
R197, R200, R201, R203: 47R; R6332W
R199: 3.3K; R6332W
R205: TRIM

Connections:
+12V: IC5.4 (V+), IC6.4 (V+), IC7.4 (V+), IC8.4 (V+), IC9.4 (V+), IC10.4 (V+), IC11.4 (V+), IC12.4 (V+), IC14.4 (V+), IC15.4 (V+), IC16.4 (V+), IC17.4 (V+); also elsewhere on the board
-12V: IC5.11 (V-), IC6.11 (V-), IC7.11 (V-), IC8.11 (V-), IC9.11 (V-), IC10.11 (V-), IC11.11 (V-), IC12.11 (V-), IC14.11 (V-), IC15.11 (V-), IC16.11 (V-), IC17.11 (V-); also elsewhere on the board
D0: IC16.12 (+IN); also elsewhere on the board
D90: IC16.3 (+IN); also elsewhere on the board
DELTA: C79.- (2), IC16.1 (OUT), R186.2, R187.1
GND: C80.+ (1), IC14.10 (+IN), IC14.12 (+IN), IC15.3 (+IN), IC15.5 (+IN), IC15.12 (+IN), IC16.5 (+IN), IC17.5 (+IN), IC17.12 (+IN), J13.3, J13.7, J13.9, J13.11, J13.13, J13.15, R196.1; also elsewhere on the board
J_DELTA: C77.- (2), IC16.14 (OUT), R183.2, R189.1, R192.1
J_SIGMA: C78.- (2), IC17.1 (OUT), R184.2, R188.1
unnamed: R199.2, R205.1 (A)
unnamed: J13.2, R181.2
unnamed: C81.+ (1), J13.4
unnamed: R187.2, R194.1
unnamed: C79.+ (1), IC16.2 (-IN), R186.1
unnamed: C85.- (2), IC17.13 (-IN), R194.2, R195.2, R204.1
unnamed: C80.- (2), IC15.10 (+IN), R185.2
unnamed: J13.5, R181.1
unnamed: C85.+ (1), IC17.14 (OUT), R203.1
unnamed: C83.- (2), IC17.6 (-IN), R190.2, R191.2, R199.1
unnamed: C78.+ (1), IC17.2 (-IN), R184.1
unnamed: C83.+ (1), IC17.7 (OUT), R200.1
unnamed: IC14.8 (OUT), IC14.9 (-IN)
unnamed: R188.2, R195.1
unnamed: IC17.10 (+IN), R192.2, R196.2
unnamed: C76.+ (1), IC16.9 (-IN), R182.1
unnamed: IC14.13 (-IN), IC14.14 (OUT)
unnamed: R189.2, R191.1
unnamed: C77.+ (1), IC16.13 (-IN), R183.1
unnamed: C84.- (2), IC17.9 (-IN), R193.2, R202.1
unnamed: C84.+ (1), IC17.8 (OUT), R201.1
unnamed: C82.+ (1), IC15.9 (-IN), R198.1
unnamed: C81.- (2), C82.- (2), IC15.8 (OUT), R197.1
unnamed: J13.14, R197.2, R198.2
unnamed: J13.6, R185.1
unnamed: IC16.6 (-IN), IC16.7 (OUT)
unnamed: IC15.1 (OUT), IC15.2 (-IN)
unnamed: IC15.6 (-IN), IC15.7 (OUT)
unnamed: IC15.13 (-IN), IC15.14 (OUT)
S0: IC17.3 (+IN); also elsewhere on the board
S90: IC16.10 (+IN); also elsewhere on the board
SIGMA: C76.- (2), IC16.8 (OUT), R182.2, R190.1, R193.1
W: J13.1, J13.8, R200.2, R205.2 (E); also elsewhere on the board
X: J13.10, R201.2, R202.2
Y: J13.12, R203.2, R204.2

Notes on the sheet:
Four signals from the phase-sequence matrix are buffered with high impedance buffers. These are S_0 S_90, D_0 and D_90. When viewed on an oscilloscope, S_0 comes 90° before S_90 and so S_0 is used as the 90° phase advance signal J_SIGMA. The same applies to D_0 andJ_DELTA. This gives the required s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
